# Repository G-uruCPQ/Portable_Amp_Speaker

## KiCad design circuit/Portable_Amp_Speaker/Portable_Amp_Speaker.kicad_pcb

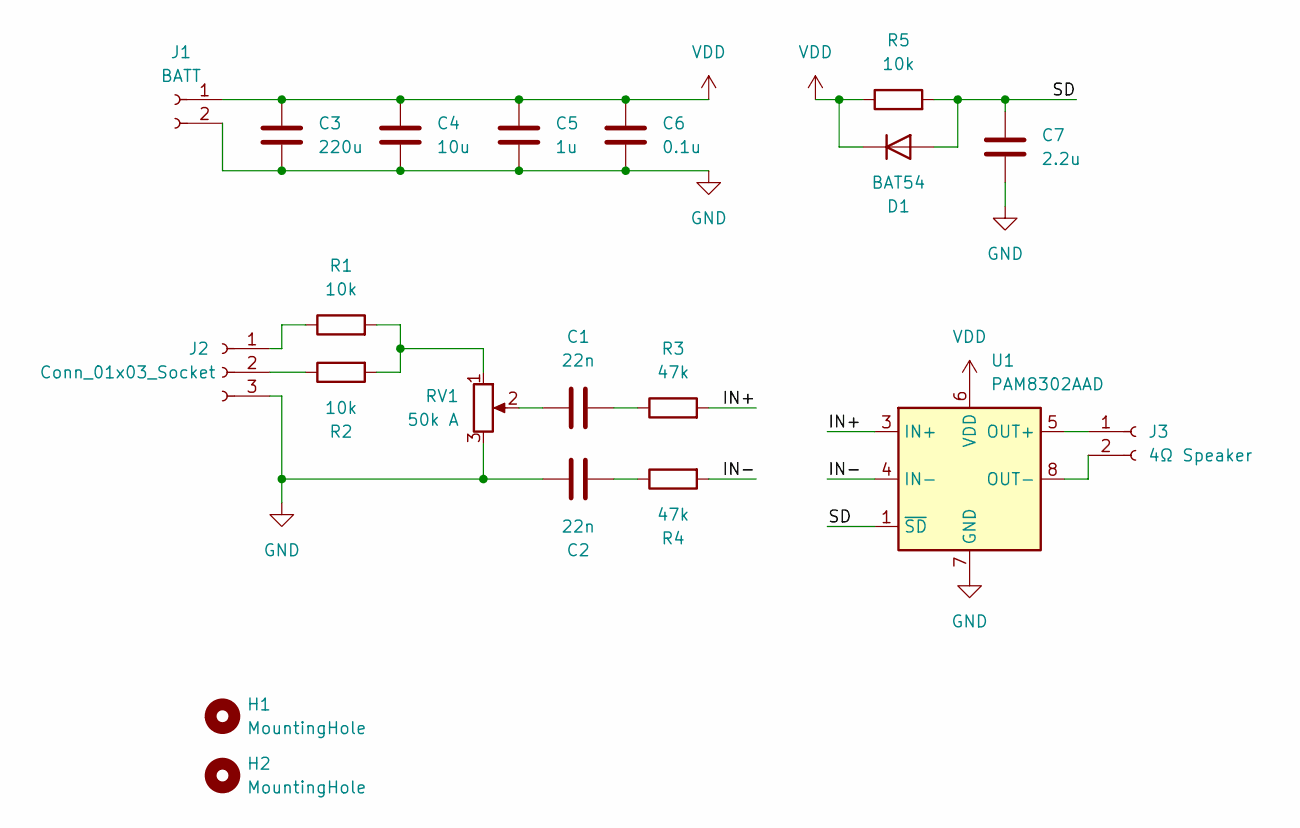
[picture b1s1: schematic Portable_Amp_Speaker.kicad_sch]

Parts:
C1, C2: 22n; C_0603_1608Metric
C3: 220u; CP_Radial_D6.3mm_P2.50mm
C4: 10u; C_0603_1608Metric
C5: 1u; C_0603_1608Metric
C6: 0.1u; C_0603_1608Metric
C7: 2.2u; C_0603_1608Metric
D1: BAT54; D_SOD-523
H1, H2: MountingHole; MountingHole_2.7mm_M2.5
J1: BATT; PinSocket_1x02_P2.54mm_Vertical
J2: Conn_01x03_Socket; PinSocket_1x03_P2.54mm_Vertical
J3: 4Ω Speaker; PinSocket_1x02_P2.54mm_Vertical
R1, R2, R5: 10k; R_0603_1608Metric
R3, R4: 47k; R_0603_1608Metric
RV1: 50k A; PinHeader_1x03_P2.54mm_Vertical
U1: PAM8302AAD; SOIC-8_3.9x4.9mm_P1.27mm

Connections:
/IN+: R3.2, U1.3 (IN+)
/IN-: R4.2, U1.4 (IN-)
/SD: C7.1, D1.2 (A), R5.2, U1.1 (~SD)
GND: C2.1, C3.2, C4.2, C5.2, C6.2, C7.2, J1.2, J2.3, RV1.3, U1.7 (GND)
unnamed: C1.1, RV1.2
unnamed: C1.2, R3.1
unnamed: C2.2, R4.1
unnamed: J2.1, R1.1
unnamed: J2.2, R2.1
unnamed: J3.1, U1.5 (OUT+)
unnamed: J3.2, U1.8 (OUT-)
unnamed: R1.2, R2.2, RV1.1
VDD: C3.1, C4.1, C5.1, C6.1, D1.1 (K), J1.1, R5.1, U1.6 (VDD)

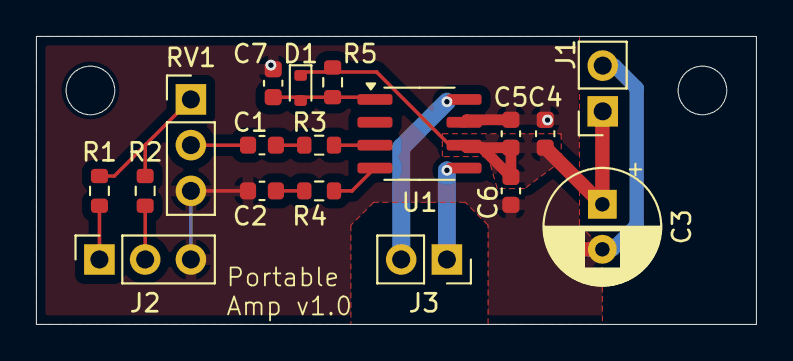
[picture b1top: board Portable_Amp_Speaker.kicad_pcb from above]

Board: 2 copper layers, 40.0 x 16.0 mm, 20 parts (0 on the bottom side), 13 nets.
